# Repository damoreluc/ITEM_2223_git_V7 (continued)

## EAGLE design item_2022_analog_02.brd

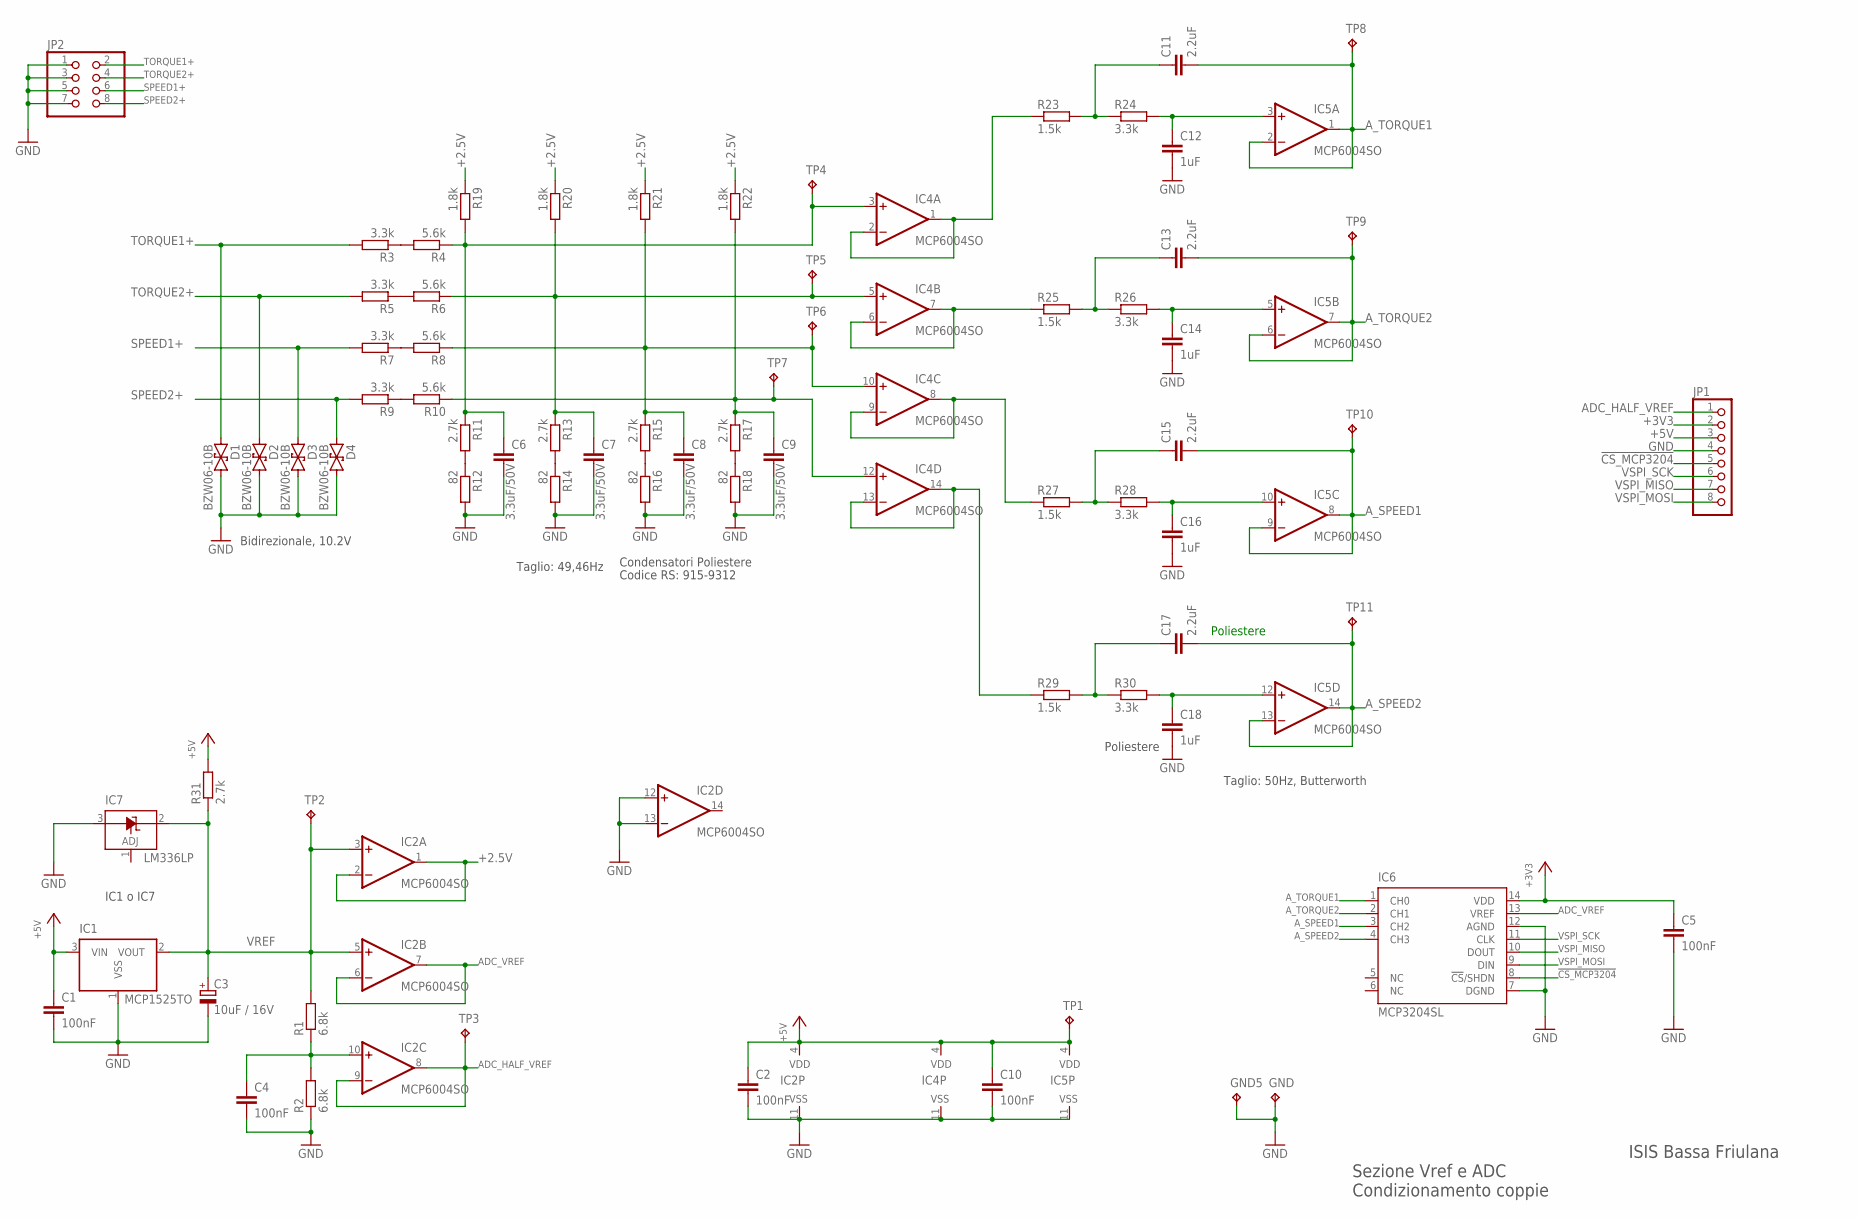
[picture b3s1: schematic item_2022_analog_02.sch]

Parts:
C1, C2, C4, C5, C10: 100nF; C0805
C3: 10uF / 16V; PANASONIC_C
C6, C7, C8, C9: 3.3uF/50V; C0805
C11, C13, C15, C17: 2.2uF; C0805
C12, C14, C16, C18: 1uF; C0805
D1, D2, D3, D4: BZW06-10B; F126Z12
GND, GND5: TPTP18SQ; TP18SQ
IC1: MCP1525TO; TO92
IC2, IC4, IC5: MCP6004SO; SO14
IC6: MCP3204SL; SO14
IC7: LM336LP; TO92
JP1: PINHD-1X8; 1X08
JP2: PINHD-2X4; 2X04
R1, R2: 6.8k; R0805
R3, R5, R9, R24, R26, R28, R30: 3.3k; R0805
R4, R6, R8, R10: 5.6k; R0805
R7: 3.3k; M0805
R11, R13, R15, R17, R31: 2.7k; R0805
R12, R14, R16, R18: 82; R0805
R19, R20, R21, R22: 1.8k; R0805
R23, R25, R27, R29: 1.5k; R0805
TP1, TP2, TP3: TPTP16R; TP16R
TP4, TP5, TP6, TP7, TP8, TP9, TP10, TP11: TPTP14R; TP14R

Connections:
!CS_MCP3204!: IC6.8 (!CS!/SHDN), JP1.5
+2.5V: IC2.1 (OUT), IC2.2 (-IN), R19.1, R20.1, R21.1, R22.1
+3V3: C5.1, IC6.14 (VDD), JP1.2
+5V: C1.1, C2.1, C10.1, IC1.3 (VIN), IC2.4 (VDD), IC4.4 (VDD), IC5.4 (VDD), JP1.3, R31.2, TP1.TP
ADC_HALF_VREF: IC2.8 (OUT), IC2.9 (-IN), JP1.1, TP3.TP
ADC_VREF: IC2.6 (-IN), IC2.7 (OUT), IC6.13 (VREF)
A_SPEED1: C15.2, IC5.8 (OUT), IC5.9 (-IN), IC6.3 (CH2), TP10.TP
A_SPEED2: C17.2, IC5.13 (-IN), IC5.14 (OUT), IC6.4 (CH3), TP11.TP
A_TORQUE1: C11.2, IC5.1 (OUT), IC5.2 (-IN), IC6.1 (CH0), TP8.TP
A_TORQUE2: C13.2, IC5.6 (-IN), IC5.7 (OUT), IC6.2 (CH1), TP9.TP
GND: C1.2, C2.2, C3.-, C4.2, C5.2, C6.2, C7.2, C8.2, C9.2, C10.2, C12.2, C14.2, C16.2, C18.2, D1.C (2), D2.C (2), D3.C (2), D4.C (2), GND.TP, GND5.TP, IC1.1 (VSS), IC2.11 (VSS), IC2.12 (+IN), IC2.13 (-IN), IC4.11 (VSS), IC5.11 (VSS), IC6.7 (DGND), IC6.12 (AGND), IC7.3 (A), JP1.4, JP2.1, JP2.3, JP2.5, JP2.7, R2.1, R12.2, R14.2, R16.2, R18.2
unnamed: C4.1, IC2.10 (+IN), R1.1, R2.2
unnamed: R3.1, R4.2
unnamed: R5.1, R6.2
unnamed: R7.1, R8.2
unnamed: R9.1, R10.2
unnamed: R11.2, R12.1
unnamed: C6.1, IC4.3 (+IN), R4.1, R11.1, R19.2, TP4.TP
unnamed: R13.2, R14.1
unnamed: R15.2, R16.1
unnamed: R17.2, R18.1
unnamed: C7.1, IC4.5 (+IN), R6.1, R13.1, R20.2, TP5.TP
unnamed: C8.1, IC4.10 (+IN), R8.1, R15.1, R21.2, TP6.TP
unnamed: C9.1, IC4.12 (+IN), R10.1, R17.1, R22.2, TP7.TP
unnamed: IC4.1 (OUT), IC4.2 (-IN), R23.1
unnamed: IC4.6 (-IN), IC4.7 (OUT), R25.1
unnamed: IC4.8 (OUT), IC4.9 (-IN), R27.1
unnamed: IC4.13 (-IN), IC4.14 (OUT), R29.1
unnamed: C11.1, R23.2, R24.1
unnamed: C12.1, IC5.3 (+IN), R24.2
unnamed: C13.1, R25.2, R26.1
unnamed: C14.1, IC5.5 (+IN), R26.2
unnamed: C15.1, R27.2, R28.1
unnamed: C16.1, IC5.10 (+IN), R28.2
unnamed: C17.1, R29.2, R30.1
unnamed: C18.1, IC5.12 (+IN), R30.2
SPEED1+: D3.A (1), JP2.6, R7.2
SPEED2+: D4.A (1), JP2.8, R9.2
TORQUE1+: D1.A (1), JP2.2, R3.2
TORQUE2+: D2.A (1), JP2.4, R5.2
VREF: C3.+, IC1.2 (VOUT), IC2.3 (+IN), IC2.5 (+IN), IC7.2 (C), R1.2, R31.1, TP2.TP
VSPI_MISO: IC6.10 (DOUT), JP1.7
VSPI_MOSI: IC6.9 (DIN), JP1.8
VSPI_SCK: IC6.11 (CLK), JP1.6

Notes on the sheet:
Sezione Vref e ADC Condizionamento coppie
ISIS Bassa Friulana
Condensatori Poliestere
Taglio: 50Hz, Butterworth
Poliestere
Taglio: 49,46Hz
Bidirezionale, 10.2V
Codice RS: 915-9312
IC1 o IC7

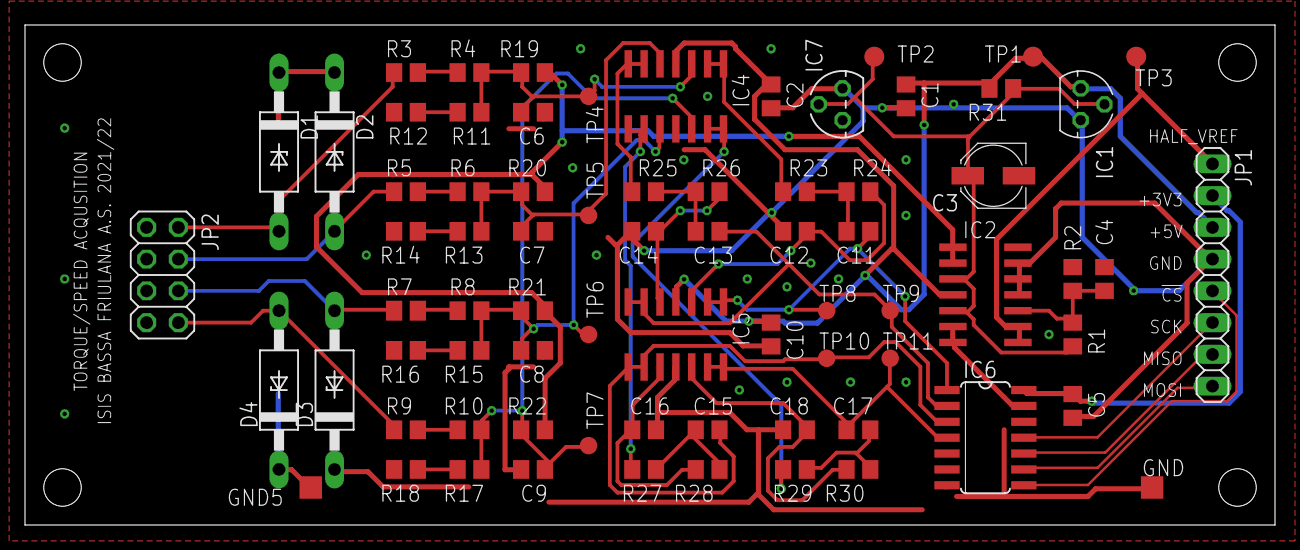
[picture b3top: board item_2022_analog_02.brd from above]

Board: 2 copper layers, 100.0 x 40.0 mm, 74 parts (0 on the bottom side), 44 nets.

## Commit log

2023-01-22 base
2023-01-22 aggiunta su sch condizionamento coppie
2023-01-22 aggiunta su brd cond coppie da sbrogliare
2023-01-28 place pcb components on grid
2023-01-28 changed PGA inputs
2023-01-28 routing with changed PGA inputs
2023-01-28 routing with corrected pads
2023-01-28 create gerber files
2023-01-29 loghi
2023-01-29 corretto layer 21
2023-01-29 corretto layer 21 e creato gerber
2023-01-29 cambio package elettrolitici smd
2023-02-02 migliorate piste su D1
2023-02-02 spostati BZW su Frontend da motherboard
2023-02-03 MCP6S28 DIL
2023-02-03 Aggiornato frontend
2023-02-04 Retrace piano GND in Motherboard
2023-02-04 Siglatura scheda FRONTEND
2023-02-04 PDF con siglatura scheda FRONTEND
2023-02-04 FrontEnd con PE
2023-02-06 corretto diametro SSD1306 e RTD
2023-02-11 Gerber ordered on JLCPCB
2023-02-26 BOM in html
2023-03-24 migliorate quote
2023-03-24 Aggiungi generatore Udine
2023-05-12 Corretto pinout MCP1525
